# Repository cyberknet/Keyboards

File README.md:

# Keyboards

##  Natural Keyboard
Custom Mechanical Keyboard PCB that is designed to have a MS Natural/Ergonomic layout. Never had PCBs fabricated, please reference or use at your own risk. [More Info](https://github.com/cyberknet/Keyboards/tree/main/Natural)

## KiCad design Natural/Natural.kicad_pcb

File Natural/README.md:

## Schematic

## PCB Front

## PCB Reverse

## Render Front

## Render Reverse

## BOM
TBD

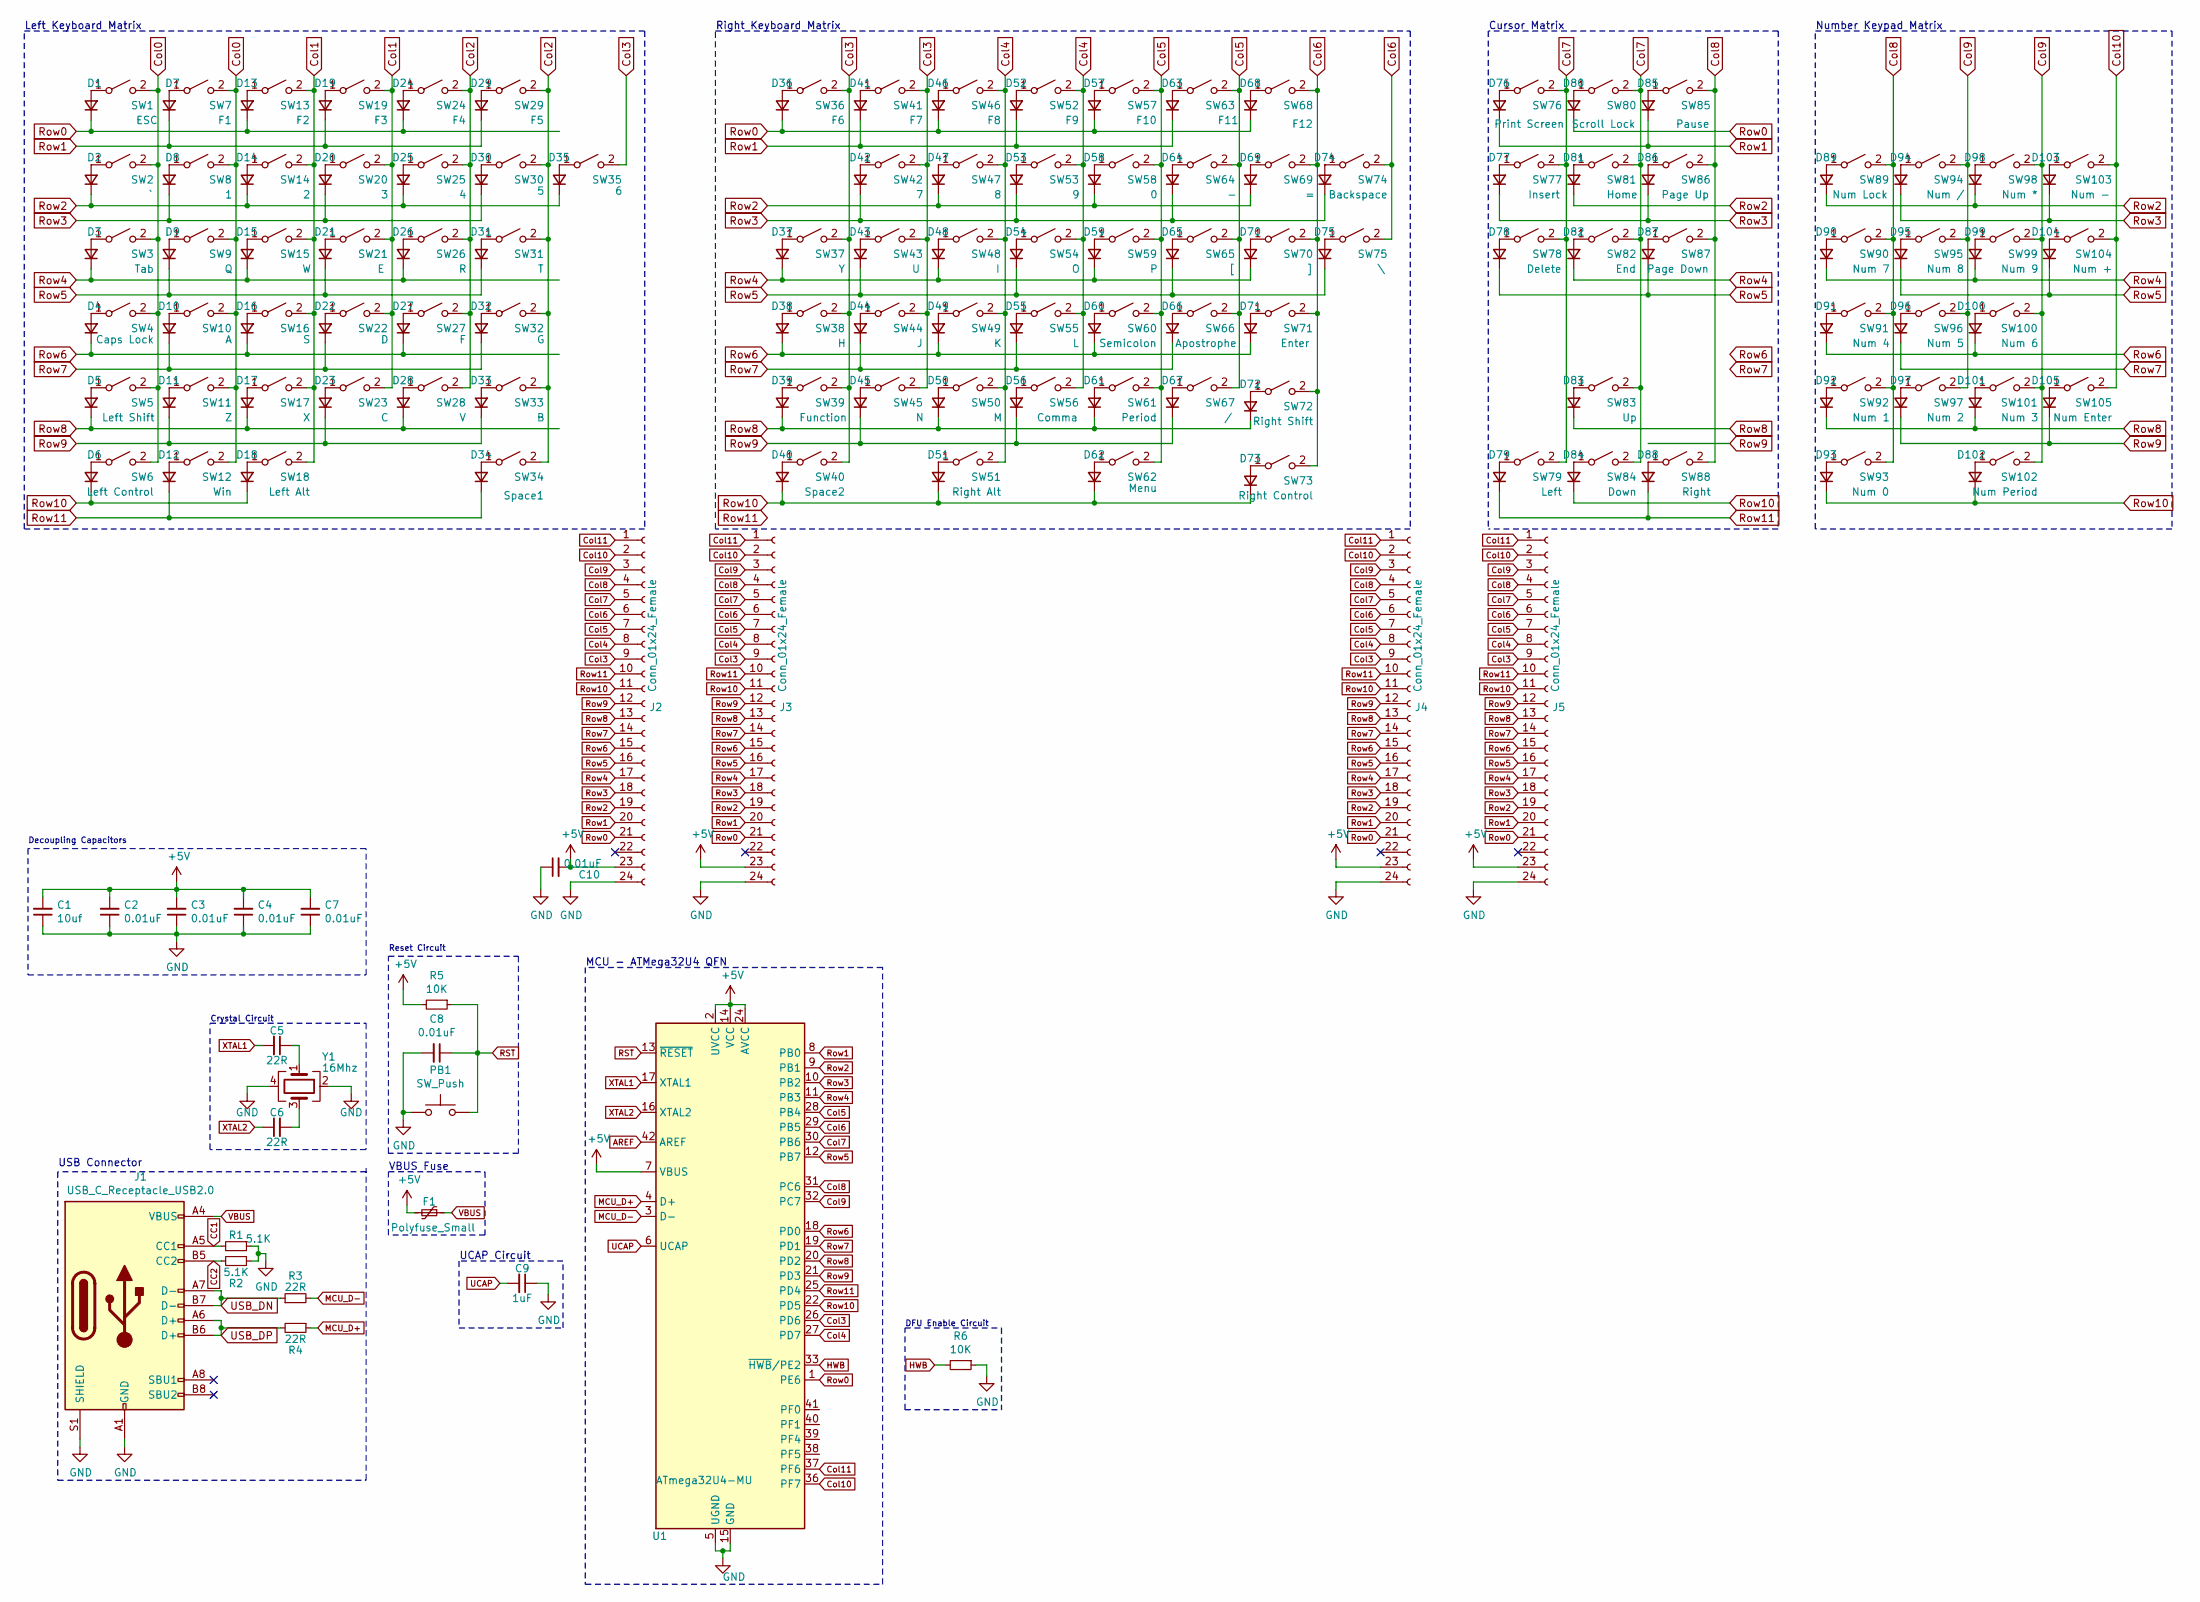
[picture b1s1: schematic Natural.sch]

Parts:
C1: 10uf; C_0402_1005Metric; Part Number C15525
C2, C3, C4, C7, C8, C10: 0.01uF; C_0402_1005Metric; Part Number C1525
C5, C6: 22R; C_0402_1005Metric; Part Number C25092
C9: 1uF; C_0402_1005Metric; Part Number C52923
D1, D2, D3, D4, D5, D6, D7, D8, D9, D10, D11, D12, D13, D14, D15, D16, D17, D18, D19, D20, D21, D22, D23, D24, D25, D26, D27, D28, D29, D30, D31, D32, D33, D34, D35, D36, D37, D38, D39, D40, D41, D42, D43, D44, D45, D46, D47, D48, D49, D50, D51, D52, D53, D54, D55, D56, D57, D58, D59, D60, D61, D62, D63, D64, D65, D66, D67, D68, D69, D70, D71, D72, D73, D74, D75, D76, D77, D78, D79, D80, D81, D82, D83, D84, D85, D86, D87, D88, D89, D90, D91, D92, D93, D94, D95, D96, D97, D98, D99, D100, D101, D102, D103, D104, D105: 1N4148W; D_SOD-123; Part Number C81598
F1: Polyfuse_Small; Fuse_1206_3216Metric
J1: USB_C_Receptacle_USB2.0; USB_C_GCT_USB4085; Part Number USB4085-GF-A
J2, J3, J4, J5: Conn_01x24_Female; PinHeader_2x12_P2.54mm_Vertical
PB1: SW_Push; SW_Push_1P1T_NO_6x6mm_H9.5mm; Part Number C273519
R1, R2: 5.1K; R_0402_1005Metric; Part Number C25744
R3, R4: 22R; R_0402_1005Metric; Part Number C25092
R5, R6: 10K; R_0402_1005Metric; Part Number C25744
SW1: ESC; SW_Cherry_MX_1.00u_PCB
SW2: `; SW_Cherry_MX_1.25u_PCB
SW3: Tab; SW_Cherry_MX_1.50u_PCB
SW4: Caps Lock; SW_Cherry_MX_1.75u_PCB
SW5: Left Shift; SW_Cherry_MX_2.00u_PCB
SW6: Left Control; SW_Cherry_MX_1.75u_PCB
SW7: F1; SW_Cherry_MX_1.00u_PCB
SW8: 1; SW_Cherry_MX_1.00u_PCB
SW9: Q; SW_Cherry_MX_1.00u_PCB
SW10: A; SW_Cherry_MX_1.00u_PCB
SW11: Z; SW_Cherry_MX_1.00u_PCB
SW12: Win; SW_Cherry_MX_1.50u_PCB
SW13: F2; SW_Cherry_MX_1.00u_PCB
SW14: 2; SW_Cherry_MX_1.00u_PCB
SW15: W; SW_Cherry_MX_1.00u_PCB
SW16: S; SW_Cherry_MX_1.00u_PCB
SW17: X; SW_Cherry_MX_1.00u_PCB
SW18: Left Alt; SW_Cherry_MX_1.50u_PCB
SW19: F3; SW_Cherry_MX_1.00u_PCB
SW20: 3; SW_Cherry_MX_1.00u_PCB
SW21: E; SW_Cherry_MX_1.00u_PCB
SW22: D; SW_Cherry_MX_1.00u_PCB
SW23: C; SW_Cherry_MX_1.00u_PCB
SW24: F4; SW_Cherry_MX_1.00u_PCB
SW25: 4; SW_Cherry_MX_1.00u_PCB
SW26: R; SW_Cherry_MX_1.00u_PCB
SW27: F; SW_Cherry_MX_1.00u_PCB
SW28: V; SW_Cherry_MX_1.00u_PCB
SW29: F5; SW_Cherry_MX_1.00u_PCB
SW30: 5; SW_Cherry_MX_1.00u_PCB
SW31: T; SW_Cherry_MX_1.00u_PCB
SW32: G; SW_Cherry_MX_1.00u_PCB
SW33: B; SW_Cherry_MX_1.00u_PCB
SW34: Space1; SW_Cherry_MX_2.75u_PCB
SW35: 6; SW_Cherry_MX_1.00u_PCB
SW36: F6; SW_Cherry_MX_1.00u_PCB
SW37: Y; SW_Cherry_MX_1.00u_PCB
SW38: H; SW_Cherry_MX_1.00u_PCB
SW39: Function; SW_Cherry_MX_1.00u_PCB
SW40: Space2; SW_Cherry_MX_2.75u_PCB
SW41: F7; SW_Cherry_MX_1.00u_PCB
SW42: 7; SW_Cherry_MX_1.00u_PCB
SW43: U; SW_Cherry_MX_1.00u_PCB
SW44: J; SW_Cherry_MX_1.00u_PCB
SW45: N; SW_Cherry_MX_1.00u_PCB
SW46: F8; SW_Cherry_MX_1.00u_PCB
SW47: 8; SW_Cherry_MX_1.00u_PCB
SW48: I; SW_Cherry_MX_1.00u_PCB
SW49: K; SW_Cherry_MX_1.00u_PCB
SW50: M; SW_Cherry_MX_1.00u_PCB
SW51: Right Alt; SW_Cherry_MX_1.75u_PCB
SW52: F9; SW_Cherry_MX_1.00u_PCB
SW53: 9; SW_Cherry_MX_1.00u_PCB
SW54: O; SW_Cherry_MX_1.00u_PCB
SW55: L; SW_Cherry_MX_1.00u_PCB
SW56: Comma; SW_Cherry_MX_1.00u_PCB
SW57: F10; SW_Cherry_MX_1.00u_PCB
SW58: 0; SW_Cherry_MX_1.00u_PCB
SW59: P; SW_Cherry_MX_1.00u_PCB
SW60: Semicolon; SW_Cherry_MX_1.00u_PCB
SW61: Period; SW_Cherry_MX_1.00u_PCB
SW62: Menu; SW_Cherry_MX_1.75u_PCB
SW63: F11; SW_Cherry_MX_1.00u_PCB
SW64: -; SW_Cherry_MX_1.00u_PCB
SW65: [; SW_Cherry_MX_1.00u_PCB
SW66: Apostrophe; SW_Cherry_MX_1.00u_PCB
SW67: /; SW_Cherry_MX_1.00u_PCB
SW68: F12; SW_Cherry_MX_1.00u_PCB
SW69: =; SW_Cherry_MX_1.00u_PCB
SW70: ]; SW_Cherry_MX_1.00u_PCB
SW71: Enter; SW_Cherry_MX_1.75u_PCB
SW72: Right Shift; SW_Cherry_MX_2.00u_PCB
SW73: Right Control; SW_Cherry_MX_1.75u_PCB
SW74: Backspace; SW_Cherry_MX_2.00u_PCB
SW75: \\; SW_Cherry_MX_1.25u_PCB
SW76: Print Screen; SW_Cherry_MX_1.00u_PCB
SW77: Insert; SW_Cherry_MX_1.00u_PCB
SW78: Delete; SW_Cherry_MX_1.00u_PCB
SW79: Left; SW_Cherry_MX_1.00u_PCB
SW80: Scroll Lock; SW_Cherry_MX_1.00u_PCB
SW81: Home; SW_Cherry_MX_1.00u_PCB
SW82: End; SW_Cherry_MX_1.00u_PCB
SW83: Up; SW_Cherry_MX_1.00u_PCB
SW84: Down; SW_Cherry_MX_1.00u_PCB
SW85: Pause; SW_Cherry_MX_1.00u_PCB
SW86: Page Up; SW_Cherry_MX_1.00u_PCB
SW87: Page Down; SW_Cherry_MX_1.00u_PCB
SW88: Right; SW_Cherry_MX_1.00u_PCB
SW89: Num Lock; SW_Cherry_MX_1.00u_PCB
SW90: Num 7; SW_Cherry_MX_1.00u_PCB
SW91: Num 4; SW_Cherry_MX_1.00u_PCB
SW92: Num 1; SW_Cherry_MX_1.00u_PCB
SW93: Num 0; SW_Cherry_MX_2.00u_PCB
SW94: Num /; SW_Cherry_MX_1.00u_PCB
SW95: Num 8; SW_Cherry_MX_1.00u_PCB
SW96: Num 5; SW_Cherry_MX_1.00u_PCB
SW97: Num 2; SW_Cherry_MX_1.00u_PCB
SW98: Num *; SW_Cherry_MX_1.00u_PCB
SW99: Num 9; SW_Cherry_MX_1.00u_PCB
SW100: Num 6; SW_Cherry_MX_1.00u_PCB
SW101: Num 3; SW_Cherry_MX_1.00u_PCB
SW102: Num Period; SW_Cherry_MX_1.00u_PCB
SW103: Num -; SW_Cherry_MX_1.00u_PCB
SW104: Num +; SW_Cherry_MX_2.00u_Vertical_PCB
SW105: Num Enter; SW_Cherry_MX_2.00u_Vertical_PCB
U1: ATmega32U4-MU; QFN-44-1EP_7x7mm_P0.5mm_EP5.2x5.2mm; Part Number C45874
Y1: 16Mhz; Crystal_SMD_TXC_7M-4Pin_3.2x2.5mm; PartNumber C13738

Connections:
+5V: C1.2, C2.2, C3.2, C4.2, C7.2, C10.2, F1.2, J2.23, J3.23, J4.23, J5.23, R5.2, U1.2 (UVCC), U1.7 (VBUS), U1.14 (VCC), U1.24 (AVCC), U1.34 (VCC), U1.44 (AVCC)
AREF: U1.42 (AREF)
CC1: J1.A5 (CC1), R1.2
CC2: J1.B5 (CC2), R2.2
Col0: SW1.2 (B), SW2.2 (B), SW3.2 (B), SW4.2 (B), SW5.2 (B), SW6.2 (B), SW7.2 (B), SW8.2 (B), SW9.2 (B), SW10.2 (B), SW11.2 (B), SW12.2 (B)
Col1: SW13.2 (B), SW14.2 (B), SW15.2 (B), SW16.2 (B), SW17.2 (B), SW18.2 (B), SW19.2 (B), SW20.2 (B), SW21.2 (B), SW22.2 (B), SW23.2 (B)
Col2: SW24.2 (B), SW25.2 (B), SW26.2 (B), SW27.2 (B), SW28.2 (B), SW29.2 (B), SW30.2 (B), SW31.2 (B), SW32.2 (B), SW33.2 (B), SW34.2 (B)
Col3: J2.9, J3.9, J4.9, J5.9, SW35.2 (B), SW36.2 (B), SW37.2 (B), SW38.2 (B), SW39.2 (B), SW40.2 (B), SW41.2 (B), SW42.2 (B), SW43.2 (B), SW44.2 (B), SW45.2 (B), U1.26 (PD6)
Col4: J2.8, J3.8, J4.8, J5.8, SW46.2 (B), SW47.2 (B), SW48.2 (B), SW49.2 (B), SW50.2 (B), SW51.2 (B), SW52.2 (B), SW53.2 (B), SW54.2 (B), SW55.2 (B), SW56.2 (B), U1.27 (PD7)
Col5: J2.7, J3.7, J4.7, J5.7, SW57.2 (B), SW58.2 (B), SW59.2 (B), SW60.2 (B), SW61.2 (B), SW62.2 (B), SW63.2 (B), SW64.2 (B), SW65.2 (B), SW66.2 (B), SW67.2 (B), U1.28 (PB4)
Col6: J2.6, J3.6, J4.6, J5.6, SW68.2 (B), SW69.2 (B), SW70.2 (B), SW71.2 (B), SW72.2 (B), SW73.2 (B), SW74.2 (B), SW75.2 (B), U1.29 (PB5)
Col7: J2.5, J3.5, J4.5, J5.5, SW76.2 (B), SW77.2 (B), SW78.2 (B), SW79.2 (B), SW80.2 (B), SW81.2 (B), SW82.2 (B), SW83.2 (B), SW84.2 (B), U1.30 (PB6)
Col8: J2.4, J3.4, J4.4, J5.4, SW85.2 (B), SW86.2 (B), SW87.2 (B), SW88.2 (B), SW89.2 (B), SW90.2 (B), SW91.2 (B), SW92.2 (B), SW93.2 (B), U1.31 (PC6)
Col9: J2.3, J3.3, J4.3, J5.3, SW94.2 (B), SW95.2 (B), SW96.2 (B), SW97.2 (B), SW98.2 (B), SW99.2 (B), SW100.2 (B), SW101.2 (B), SW102.2 (B), U1.32 (PC7)
Col10: J2.2, J3.2, J4.2, J5.2, SW103.2 (B), SW104.2 (B), SW105.2 (B), U1.36 (PF7)
Col11: J2.1, J3.1, J4.1, J5.1, U1.37 (PF6)
GND: C1.1, C2.1, C3.1, C4.1, C7.1, C8.2, C9.1, C10.1, J1.A1 (GND), J1.A12 (GND), J1.B1 (GND), J1.B12 (GND), J1.S1 (SHIELD), J2.24, J3.24, J4.24, J5.24, PB1.1, R1.1, R2.1, R6.1, U1.5 (UGND), U1.15 (GND), U1.23 (GND), U1.35 (GND), U1.43 (GND), U1.45 (GND), Y1.2, Y1.4
HWB: R6.2, U1.33 (~HWB~/PE2)
MCU_D+: R4.1, U1.4 (D+)
MCU_D-: R3.2, U1.3 (D-)
unnamed: C5.1, Y1.1
unnamed: C6.2, Y1.3
unnamed: D1.2 (A), SW1.1 (A)
unnamed: D2.2 (A), SW2.1 (A)
unnamed: D3.2 (A), SW3.1 (A)
unnamed: D4.2 (A), SW4.1 (A)
unnamed: D5.2 (A), SW5.1 (A)
unnamed: D6.2 (A), SW6.1 (A)
unnamed: D7.2 (A), SW7.1 (A)
unnamed: D8.2 (A), SW8.1 (A)
unnamed: D9.2 (A), SW9.1 (A)
unnamed: D10.2 (A), SW10.1 (A)
unnamed: D11.2 (A), SW11.1 (A)
unnamed: D12.2 (A), SW12.1 (A)
unnamed: D13.2 (A), SW13.1 (A)
unnamed: D14.2 (A), SW14.1 (A)
unnamed: D15.2 (A), SW15.1 (A)
unnamed: D16.2 (A), SW16.1 (A)
unnamed: D17.2 (A), SW17.1 (A)
unnamed: D18.2 (A), SW18.1 (A)
unnamed: D19.2 (A), SW19.1 (A)
unnamed: D20.2 (A), SW20.1 (A)
unnamed: D21.2 (A), SW21.1 (A)
unnamed: D22.2 (A), SW22.1 (A)
unnamed: D23.2 (A), SW23.1 (A)
unnamed: D24.2 (A), SW24.1 (A)
unnamed: D25.2 (A), SW25.1 (A)
unnamed: D26.2 (A), SW26.1 (A)
unnamed: D27.2 (A), SW27.1 (A)
unnamed: D28.2 (A), SW28.1 (A)
unnamed: D29.2 (A), SW29.1 (A)
unnamed: D30.2 (A), SW30.1 (A)
unnamed: D31.2 (A), SW31.1 (A)
unnamed: D32.2 (A), SW32.1 (A)
unnamed: D33.2 (A), SW33.1 (A)
unnamed: D34.2 (A), SW34.1 (A)
unnamed: D35.2 (A), SW35.1 (A)
unnamed: D36.2 (A), SW36.1 (A)
unnamed: D37.2 (A), SW37.1 (A)
unnamed: D38.2 (A), SW38.1 (A)
unnamed: D39.2 (A), SW39.1 (A)
unnamed: D40.2 (A), SW40.1 (A)
unnamed: D41.2 (A), SW41.1 (A)
unnamed: D42.2 (A), SW42.1 (A)
unnamed: D43.2 (A), SW43.1 (A)
unnamed: D44.2 (A), SW44.1 (A)
unnamed: D45.2 (A), SW45.1 (A)
unnamed: D46.2 (A), SW46.1 (A)
unnamed: D47.2 (A), SW47.1 (A)
unnamed: D48.2 (A), SW48.1 (A)
unnamed: D49.2 (A), SW49.1 (A)
unnamed: D50.2 (A), SW50.1 (A)
unnamed: D51.2 (A), SW51.1 (A)
unnamed: D52.2 (A), SW52.1 (A)
unnamed: D53.2 (A), SW53.1 (A)
unnamed: D54.2 (A), SW54.1 (A)
unnamed: D55.2 (A), SW55.1 (A)
unnamed: D56.2 (A), SW56.1 (A)
unnamed: D57.2 (A), SW57.1 (A)
unnamed: D58.2 (A), SW58.1 (A)
unnamed: D59.2 (A), SW59.1 (A)
unnamed: D60.2 (A), SW60.1 (A)
unnamed: D61.2 (A), SW61.1 (A)
unnamed: D62.2 (A), SW62.1 (A)
unnamed: D63.2 (A), SW63.1 (A)
unnamed: D64.2 (A), SW64.1 (A)
unnamed: D65.2 (A), SW65.1 (A)
unnamed: D66.2 (A), SW66.1 (A)
unnamed: D67.2 (A), SW67.1 (A)
unnamed: D68.2 (A), SW68.1 (A)
unnamed: D69.2 (A), SW69.1 (A)
unnamed: D70.2 (A), SW70.1 (A)
unnamed: D71.2 (A), SW71.1 (A)
unnamed: D72.2 (A), SW72.1 (A)
unnamed: D73.2 (A), SW73.1 (A)
unnamed: D74.2 (A), SW74.1 (A)
unnamed: D75.2 (A), SW75.1 (A)
unnamed: D76.2 (A), SW76.1 (A)
unnamed: D77.2 (A), SW77.1 (A)
unnamed: D78.2 (A), SW78.1 (A)
unnamed: D79.2 (A), SW79.1 (A)
unnamed: D80.2 (A), SW80.1 (A)
unnamed: D81.2 (A), SW81.1 (A)
unnamed: D82.2 (A), SW82.1 (A)
unnamed: D83.2 (A), SW83.1 (A)
unnamed: D84.2 (A), SW84.1 (A)
unnamed: D85.2 (A), SW85.1 (A)
unnamed: D86.2 (A), SW86.1 (A)
unnamed: D87.2 (A), SW87.1 (A)
unnamed: D88.2 (A), SW88.1 (A)
unnamed: D89.2 (A), SW89.1 (A)
unnamed: D90.2 (A), SW90.1 (A)
unnamed: D91.2 (A), SW91.1 (A)
unnamed: D92.2 (A), SW92.1 (A)
unnamed: D93.2 (A), SW93.1 (A)
unnamed: D94.2 (A), SW94.1 (A)
unnamed: D95.2 (A), SW95.1 (A)
unnamed: D96.2 (A), SW96.1 (A)
unnamed: D97.2 (A), SW97.1 (A)
unnamed: D98.2 (A), SW98.1 (A)
unnamed: D99.2 (A), SW99.1 (A)
unnamed: D100.2 (A), SW100.1 (A)
unnamed: D101.2 (A), SW101.1 (A)
unnamed: D102.2 (A), SW102.1 (A)
unnamed: D103.2 (A), SW103.1 (A)
unnamed: D104.2 (A), SW104.1 (A)
unnamed: D105.2 (A), SW105.1 (A)
RST: C8.1, PB1.2, R5.1, U1.13 (~RESET)
Row0: D1.1 (K), D13.1 (K), D24.1 (K), D36.1 (K), D46.1 (K), D57.1 (K), D68.1 (K), D80.1 (K), J2.21, J3.21, J4.21, J5.21, U1.1 (PE6)
Row1: D7.1 (K), D19.1 (K), D29.1 (K), D41.1 (K), D52.1 (K), D63.1 (K), D76.1 (K), D85.1 (K), J2.20, J3.20, J4.20, J5.20, U1.8 (PB0)
Row2: D2.1 (K), D14.1 (K), D25.1 (K), D35.1 (K), D47.1 (K), D58.1 (K), D69.1 (K), D81.1 (K), D89.1 (K), D98.1 (K), J2.19, J3.19, J4.19, J5.19, U1.9 (PB1)
Row3: D8.1 (K), D20.1 (K), D30.1 (K), D42.1 (K), D53.1 (K), D64.1 (K), D74.1 (K), D77.1 (K), D86.1 (K), D94.1 (K), D103.1 (K), J2.18, J3.18, J4.18, J5.18, U1.10 (PB2)
Row4: D3.1 (K), D15.1 (K), D26.1 (K), D37.1 (K), D48.1 (K), D59.1 (K), D70.1 (K), D82.1 (K), D90.1 (K), D99.1 (K), J2.17, J3.17, J4.17, J5.17, U1.11 (PB3)
Row5: D9.1 (K), D21.1 (K), D31.1 (K), D43.1 (K), D54.1 (K), D65.1 (K), D75.1 (K), D78.1 (K), D87.1 (K), D95.1 (K), D104.1 (K), J2.16, J3.16, J4.16, J5.16, U1.12 (PB7)
Row6: D4.1 (K), D16.1 (K), D27.1 (K), D38.1 (K), D49.1 (K), D60.1 (K), D71.1 (K), D91.1 (K), D100.1 (K), J2.15, J3.15, J4.15, J5.15, U1.18 (PD0)
Row7: D10.1 (K), D22.1 (K), D32.1 (K), D44.1 (K), D55.1 (K), D66.1 (K), D96.1 (K), J2.14, J3.14, J4.14, J5.14, U1.19 (PD1)
Row8: D5.1 (K), D17.1 (K), D28.1 (K), D39.1 (K), D50.1 (K), D61.1 (K), D72.1 (K), D83.1 (K), D92.1 (K), D101.1 (K), J2.13, J3.13, J4.13, J5.13, U1.20 (PD2)
Row9: D11.1 (K), D23.1 (K), D33.1 (K), D45.1 (K), D56.1 (K), D67.1 (K), D97.1 (K), D105.1 (K), J2.12, J3.12, J4.12, J5.12, U1.21 (PD3)
Row10: D6.1 (K), D18.1 (K), D40.1 (K), D51.1 (K), D62.1 (K), D73.1 (K), D84.1 (K), D93.1 (K), D102.1 (K), J2.11, J3.11, J4.11, J5.11, U1.22 (PD5)
Row11: D12.1 (K), D34.1 (K), D79.1 (K), D88.1 (K), J2.10, J3.10, J4.10, J5.10, U1.25 (PD4)
UCAP: C9.2, U1.6 (UCAP)
USB_DN: J1.A7 (D-), J1.B7 (D-), R3.1
USB_DP: J1.A6 (D+), J1.B6 (D+), R4.2
VBUS: F1.1, J1.A4 (VBUS), J1.A9 (VBUS), J1.B4 (VBUS), J1.B9 (VBUS)
XTAL1: C5.2, U1.17 (XTAL1)
XTAL2: C6.1, U1.16 (XTAL2)

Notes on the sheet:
Left Keyboard Matrix
Cursor Matrix
Number Keypad Matrix
MCU - ATMega32U4 QFN
Reset Circuit
DFU Enable Circuit
Decoupling Capacitors
Crystal Circuit
UCAP Circuit
USB Connector
Right Keyboard Matrix
VBUS Fuse

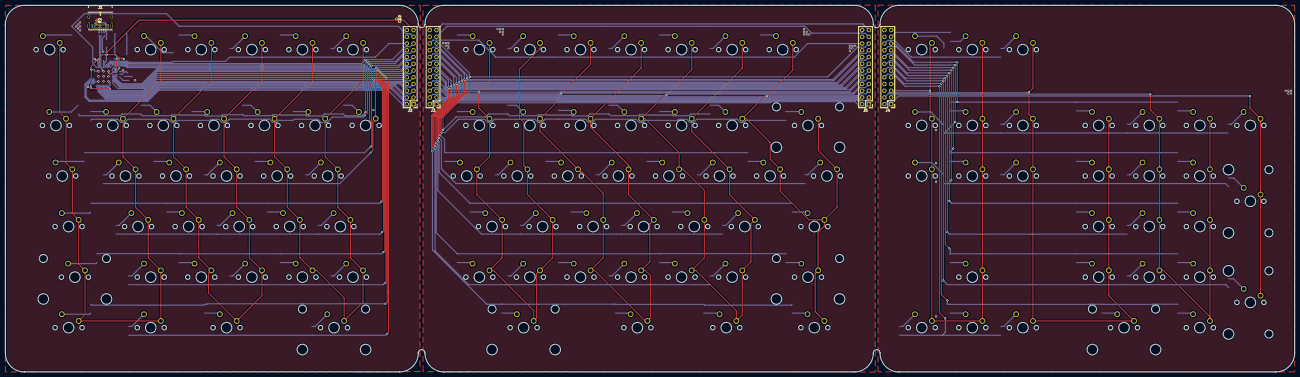
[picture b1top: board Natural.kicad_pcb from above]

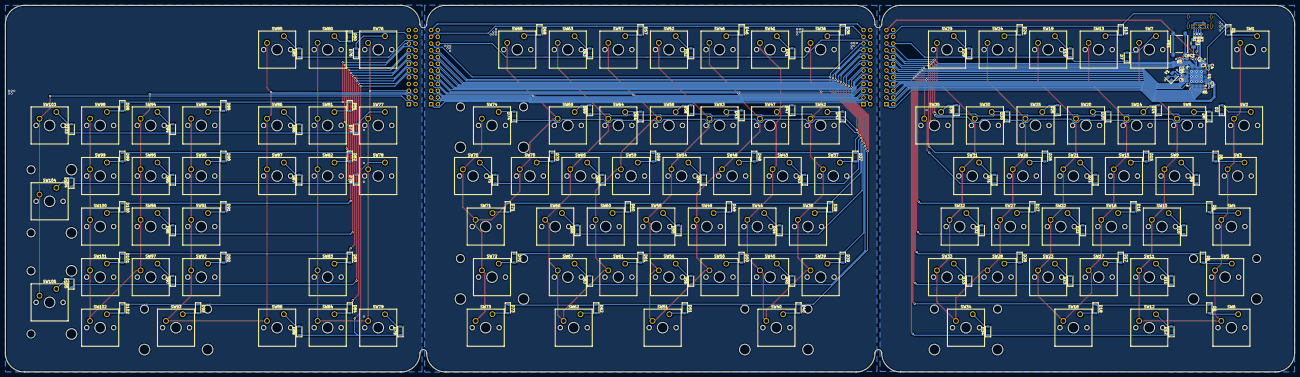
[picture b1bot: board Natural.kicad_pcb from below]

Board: 2 copper layers, 485.8 x 138.1 mm, 235 parts (228 on the bottom side), 145 nets.

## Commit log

2020-10-26 Adding Natural keyboard
2020-10-26 added board renders
2020-10-26 Update README.md
    Moved schematic/pcb images/pcb renders to Natural subfolder
2020-10-26 Removed bak files
2020-10-26 Added Keebio Parts Library
2020-10-26 Added keebio components
